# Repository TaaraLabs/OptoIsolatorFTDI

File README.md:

Opto-Isolator FTDI
==================

Opto-Isolator FTDI

[Official WebSite](https://taaralabs.eu/oi1)

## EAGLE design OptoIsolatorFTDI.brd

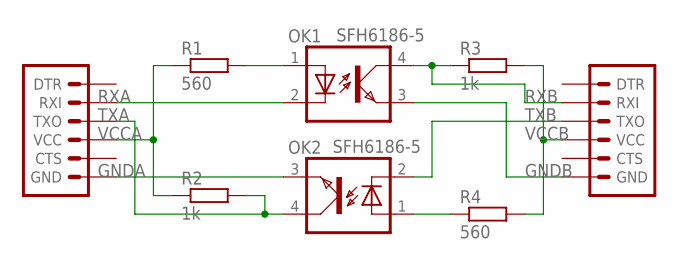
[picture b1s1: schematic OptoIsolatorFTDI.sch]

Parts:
JP1: FTDI; 1X06
JP2: FTDI_BASICPTH; 1X06
OK1, OK2: SFH6186-5; SMD4-7
R1, R4: 560; R0603
R2, R3: 1k; R0603

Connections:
GNDA: JP2.6 (GND), OK2.3 (EMIT)
GNDB: JP1.6 (GND), OK1.3 (EMIT)
unnamed: OK1.1 (A), R1.2
unnamed: OK2.1 (A), R4.1
RXA: JP2.2 (RXI), OK1.2 (C)
RXB: JP1.2 (RXI), OK1.4 (COL), R3.1
TXA: JP2.3 (TXO), OK2.4 (COL), R2.2
TXB: JP1.3 (TXO), OK2.2 (C)
VCCA: JP2.4 (VCC), R1.1, R2.1
VCCB: JP1.4 (VCC), R3.2, R4.2

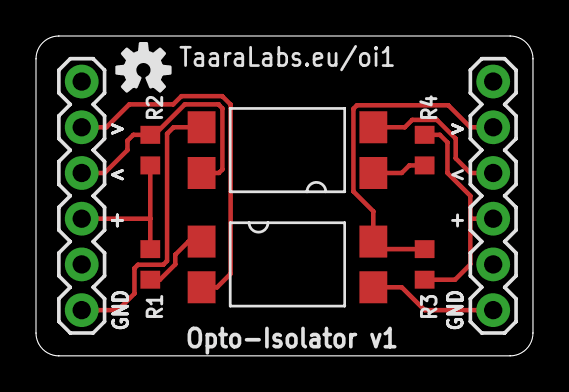
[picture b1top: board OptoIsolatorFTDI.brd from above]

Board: 2 copper layers, 27.6 x 17.8 mm, 10 parts (1 on the bottom side), 10 nets.

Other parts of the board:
U$1, U$3: OSHW-LOGO-S

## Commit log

2019-01-14 Initial upload

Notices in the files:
parts and their libraries:
SparkFun-Connectors: Licensing: Creative Commons ShareAlike 4.0 International - https://creativecommons.org/licenses/by-sa/4.0
SparkFun-Aesthetics: Licensing: CC v3.0 Share-Alike You are welcome to use this library for commercial purposes.
